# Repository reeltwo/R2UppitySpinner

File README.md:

# R2 Uppity Spinner

This is the sketch for the R2 Uppity Spinner. It depends on the Reeltwo library. You can download the latest release of the Reeltwo library here: https://github.com/reeltwo/Reeltwo/releases

Default baud rate is 9600 baud and the default I2C address is 32 (0x20). Both can be changed using the configuration commands below.

After installing your board you should run the `#PSC` calibration command.

If you want a snappy hyper caffinated periscope you should use a 6V lifter motor. If you want a slower more deliberate periscope you should use a 12V lifter motor.

# Assembling R2 Uppity Spinner PCB Part 1

# Assembling R2 Uppity Spinner PCB Part 2

## Configure commands

`#PSC`:
Calibration routine. Will store results in EEPROM if successful
*Examples*:

    #PSC

`#PZERO`:
Erase all stored sequences from EEPROM
*Examples*:

    #PZERO

`#PL`:
List all stored sequences
*Examples*:

    #PL

`#PD`[number]:
Delete numbered sequence from EEPROM
*Examples*:

    #PD0 (delete sequence 0)

`#PS`[number]:seq
Store specified sequence (seq) as number in EEPROM.
*Examples*:

	#PS1:H                        (periscope down)
	#PS2:P100                     (periscope up)
	#PS3:P100:L5:R30              (search light counter-clockwise)
	#PS4:P100,100:L7:M,80,80,2,4  (random fast)
	#PS5:P100:L7:M,50,40,5,5      (random slow)
	#PS6:A0                       (face forward)
	#PS7:P100:L5:R-30             (search light clockwise)
	#PS8:H:P50:W2:P85,35:A90,25:W2:A270,20,100:W2:P100,100:L5:R50:W4:H    (sneaky periscope)
	#PS0:H:L0:P100,5:W2:P50:W2:P85,35:A90,25:W2:A270,20,100:W2:P100,100:L5:R50:W4:H

`#PBAUD`[baudrate]
Change system baudrate. Settings will be stored in EEPROM and take affect once the board is reset.
*Examples*:

	#PBAUD9600               (set baud rate to 9600)

`#PI2C`[address]
Change system I2C address. Settings will be stored in EEPROM and take affect once the board is reset.
*Examples*:

	#PI2C128                 (set I2C address to 128)

`#PR`
Enable/disable rotary unit. This will reboot the board. The setting will persist between reboots.
*Examples*:

	#PR (toggle rotary unit on/off)

`#PNCL`
Set lifter limit switch to normally closed. Default setting.
*Examples*:

	#PNCL (lifter limit normally closed)

`#PNOL`
Set lifter limit switch to normally open.
*Examples*:

	#PNOL (lifter limit normally open)

`#PNCR`
Set rotary limit switch to normally closed. Default setting.
*Examples*:

	#PNCL (rotary limit normally closed)

`#PNOR`
Set rotary limit switch to normally open.
*Examples*:

	#PNOR (rotary limit normally open)

Lifter commands
===============

A lifter command starts with ':P' followed by one of the these. Multiple commands can be issued seperated by a colon. Only the first command needs to be prefixed with 'P':

	:PP100:W2:P0

Would raise the periscope. Wait 2 seconds. Lower the periscope. Separately the commnads would be:

	:PP100
	:PW2
	:PP0

### Play stored sequence

`S`[number]:
Sequences can be stored using #PS
*Examples*:

    #PS0:H:L0:P100,5:W2:P50,25:W2:P85,35:A90,20:W2:A270,20,100:W2:P100,100:L5:R50:W4:H

### Wait number of seconds
`W`[R]seconds:
Wait for specified number of seconds. If 'R' is specified it will randomize the wait time in the range of 1..seconds. 'seconds' is a number between 1 and 600.
*Examples*:

	:PW2    (wait 2 seconds before executing next sequence)
	:PWR    (wait random 1-6 seconds)
	:PWR10  (wait random 1-10 seconds)

### Light kit sequence
`L`number:
Light kit sequence where number is in the range 0..7

`0`: Full Cycle (default): This routine will randomly select the LED color, pattern, and speed for a random period of time.
    
`1`: Off: This setting turns ALL lights OFF. I added this to allow a microcontroller to turn off the lights without having to kill the supply power.
    
`2`: Obi Wan: The Top LED’s flash Blue, the Side LED’s are Blue, and the Main White LED’s are Random.
    
`3`: Yoda: The Top LED’s and Side LED’s fade Green On and Off.
    
`4`: Sith: The Top LED’s and Side LED’s flash Red.
    
`5`: Search Light: All LED’s are White, the Center Bright LED is ON.
    
`6`: Dagobah: This is the most screen accurate mode. The Main White LED’s are ON, the side LED’s are White, the Lower  Rectangular Red LED’s are All On, and the Rear LED’s are Blinking Red.
    
`7`: Sparkle: All White LED’s randomly Flash
    
*Examples*:

    :PL0    (full cycle)
    :PL1    (off)

### Home
`H`[speed]:
Rotates the periscope into the home position and lowers the lifter. Will retry once if rotary ends up not in home position.
*Examples*:

	:PH     (go home at minimum power)
	:PH50   (go home at 50% speed)
	:PH100  (go home at 100% speed)

### Rotate scope relative degrees
`D`[R]:
Rotate scope random relative degrees
*Examples*:

	:PDR

`D`[degrees]:
Rotate scope relative degrees positive for counter clockwise and negative for clockwise
*Examples*:

	:PD90       (rotate periscope relative 90 degrees counter clockwise)
	:PD-90      (rotate periscope relative 90 degrees clockwise)

### Rotate scope absolute degrees
`A`[R][,speed][,maxspeed]:
Rotate scope random absolute degrees
*Examples*:

	:PAR

`A`[degrees][,speed][,maxspeed]:
Rotate scope to absolute position degrees. Positive for clockwise and negative for counter clockwise. Optionally specify the speed percentage and maximum speed percentage. By default the speed used is minimum rotary power (20%). The maximum speed defaults to the same value as speed if omitted.
*Examples*:

	:PA90        (rotate periscope to 90 degrees clockwise)
	:PA270       (rotate periscope to 270 degrees clockwise)
	:PA-90       (rotate periscope to 270 degrees clockwise)
	:PA0         (rotate periscope to home position)
	:PA90,20,100 (rotate periscope to 90 degrees starting at 20% speed increasing to 100%)
	             (will mostly likely overshoot target)

### Rotate scope continously
`R`[speed]:
Spin rotary scope at specified speed percentage
*Examples*:

	:PR30       (spin periscope at 30% speed counter clockwise)
	:PR-30      (spin periscope at 30% speed clockwise)

`R`[,speed]:
Lift periscope to random position.
*Examples*:

	:PPR        (random position)
	:PPR,50     (random position at 50% speed)

### Raise/lower periscope
`P`[position][,speed]:
Lift periscope to specified position percentage.
*Examples*:

	:PP100      (raise periscope fully)
	:PP0        (lower periscope fully)
	:PP50       (raise periscope halfway)
	:PP100,100  (raise periscope fully at maximum speed)

### Movement Random Continous
`M`,lifterspeed][,rotaryspeed][,mininterval][,maxinterval]:
Animate periscope continously rotate/lift.
*Examples*:

	:M,80,80,2,4  (animate lifter 80% power, rotatary random(20%-80%), minimum interval 2 seconds for a duration of 2+random(4) seconds )
	:M,50,40,5,5  (animate lifter 50% power, rotatary random(20%-40%) power, 80% minimum interval 5 seconds for a duration of 5+5 seconds )

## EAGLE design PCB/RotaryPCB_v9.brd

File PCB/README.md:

# Electronics Design

The files were created using Fusion 360, which uses a new version of the Eagle format.

- LifterPCB.brd
- LifterPCB.sch

- RotaryPCB.brd
- RotaryPCB.sch

These files were exported in Eagle v9 compatible format.

- LifterPCB_v9.brd
- LifterPBC_v9.sch

- RotaryPCB_v9.brd
- RotaryPCB_v9.sch

This version uses thicker traces and adds a copper pour. The lifter board is a four layer board. The order of the connection pins on the rotary has changed. Do NOT use the same cable as the older board. The order was changed to allow using a silicone ribbon cable and this crimp connector:

https://www.mouser.com/ProductDetail/571-2-1761607-3

The 10 Wire silicone cable:
https://www.adafruit.com/product/3890

The dual row IDC female connectors:
https://www.amazon.com/gp/product/B07S1NFG4S

If you do not plan on using the ribbon cable there is no need to switch to this version of the lifter.

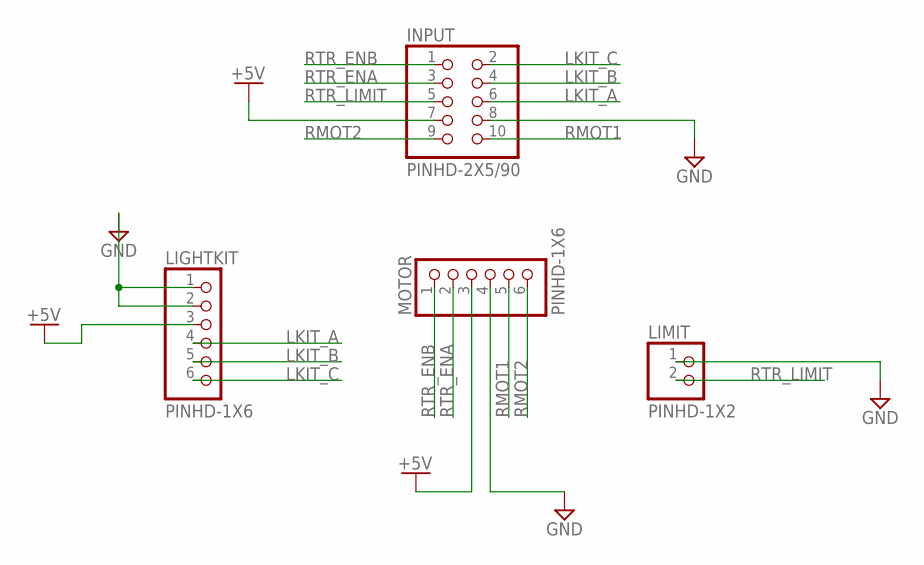
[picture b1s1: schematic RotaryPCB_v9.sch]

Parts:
INPUT: PINHD-2X5/90; 2X05/90
LIGHTKIT: PINHD-1X6; 1X06
LIMIT: PINHD-1X2; 1X02
MOTOR: PINHD-1X6; 1X06

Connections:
+5V: INPUT.7, LIGHTKIT.3, MOTOR.3
GND: INPUT.8, LIGHTKIT.1, LIGHTKIT.2, LIMIT.1, MOTOR.4
LKIT_A: INPUT.6, LIGHTKIT.4
LKIT_B: INPUT.4, LIGHTKIT.5
LKIT_C: INPUT.2, LIGHTKIT.6
RMOT1: INPUT.10, MOTOR.5
RMOT2: INPUT.9, MOTOR.6
RTR_ENA: INPUT.3, MOTOR.2
RTR_ENB: INPUT.1, MOTOR.1
RTR_LIMIT: INPUT.5, LIMIT.2

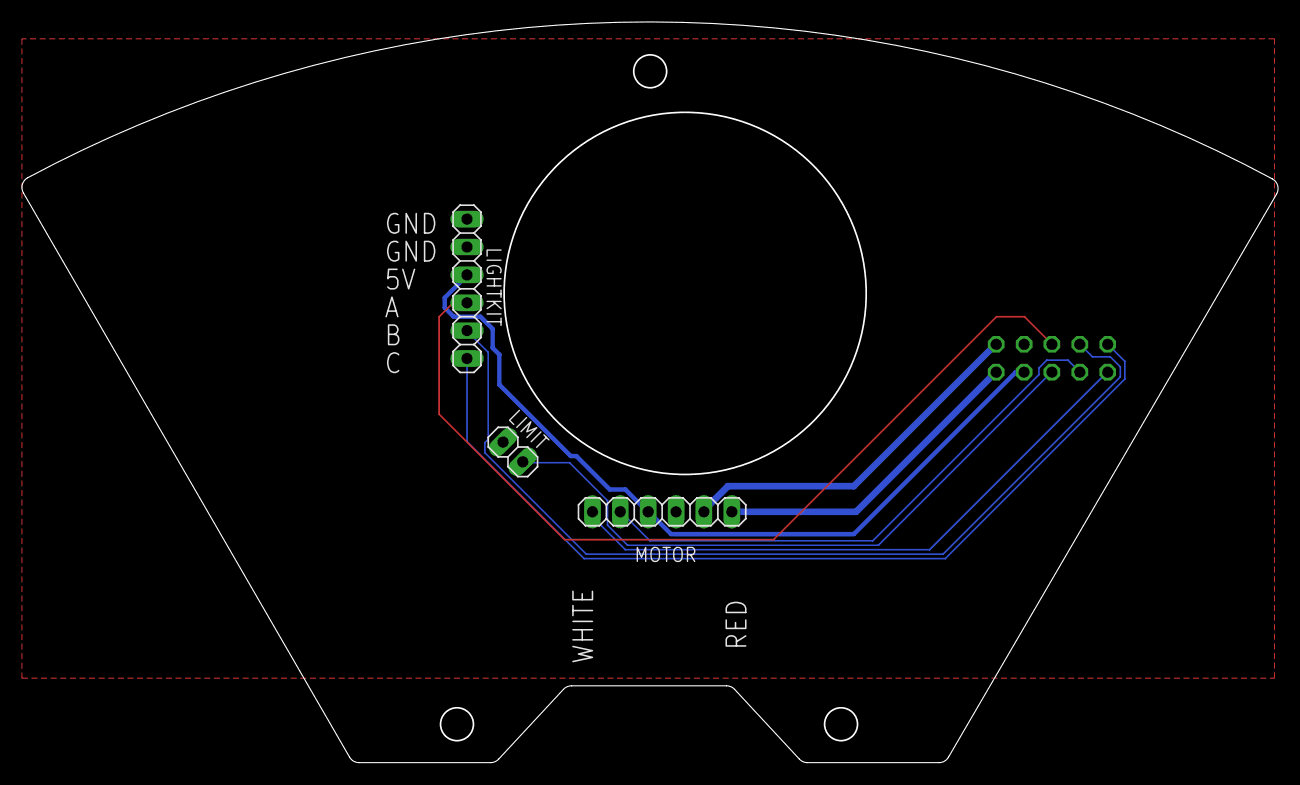
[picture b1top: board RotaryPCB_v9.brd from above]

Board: 2 copper layers, 114.5 x 67.5 mm, 4 parts (1 on the bottom side), 10 nets.

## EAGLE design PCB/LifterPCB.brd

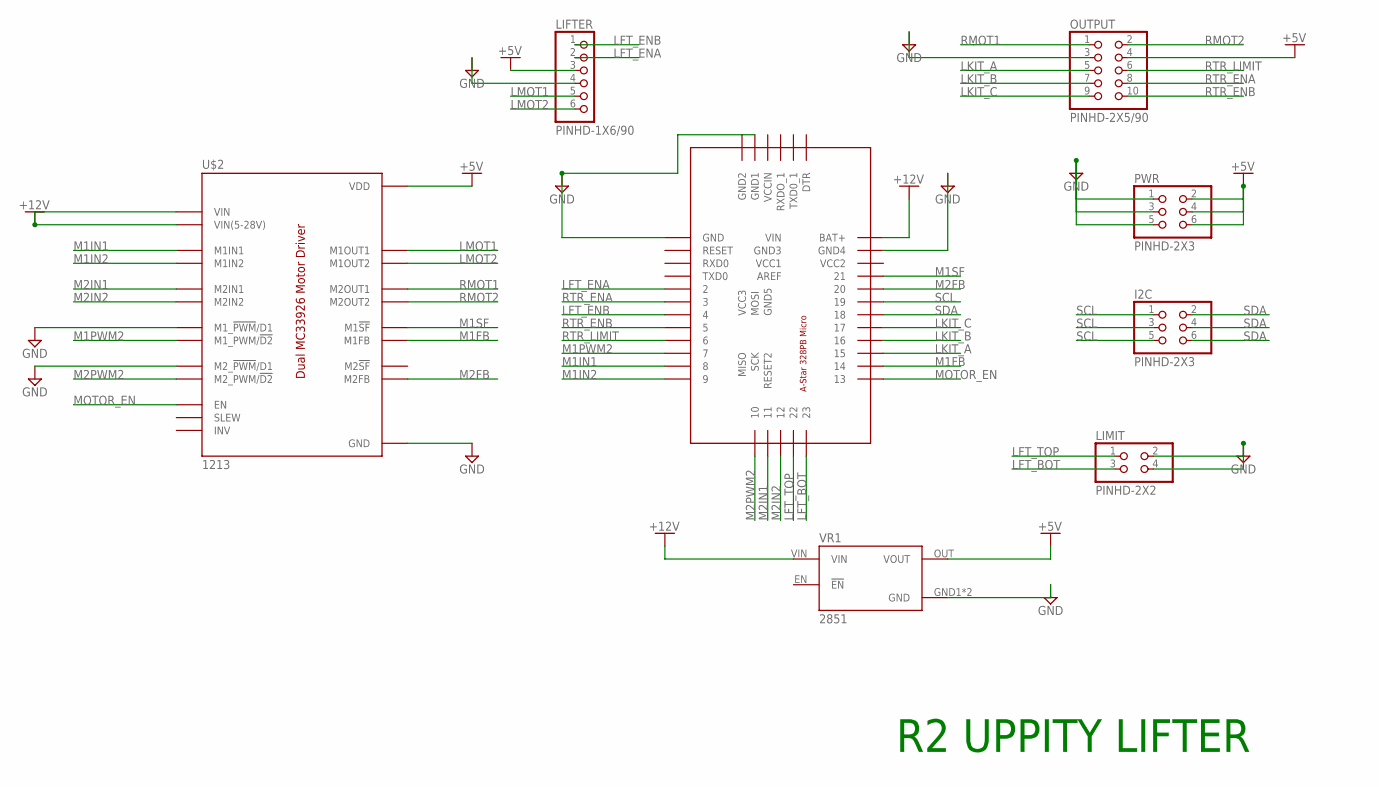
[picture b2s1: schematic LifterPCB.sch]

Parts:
I2C: PINHD-2X3; 2X03
LIFTER: PINHD-1X6/90; 1X06/90
LIMIT: PINHD-2X2; 2X02
OUTPUT: PINHD-2X5/90; 2X05/90
PWR: PINHD-2X3; 2X03
U$1: POLOLU3161
U$2: 1213
VR1: 2851; VREG_2851

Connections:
+5V: LIFTER.3, OUTPUT.4, PWR.2, PWR.4, PWR.6, U$2.VDD, U$2.VDD$1 (VDD), U$2.VDD$2 (VDD), U$2.VDD$3 (VDD), U$2.VDD$4 (VDD), U$2.VDD$5 (VDD), VR1.OUT (VOUT)
+12V: U$1.BAT+, U$2.MVIN (VIN(5-28V)), U$2.VIN, VR1.VIN
GND: LIFTER.4, LIMIT.2, LIMIT.4, OUTPUT.3, PWR.1, PWR.3, PWR.5, U$1.GND2 (GND4), U$1.GND4 (GND2), U$1.GND5 (GND1), U$1.GND6 (GND), U$2.GND, U$2.GND$1 (GND), U$2.GND$2 (GND), U$2.M1PWM1 (M1_!PWM!/D1), U$2.M2PWM1 (M2_!PWM!/D1), U$2.MGND (GND), VR1.GND1 (GND), VR1.GND2 (GND)
LFT_BOT: LIMIT.3, U$1.23
LFT_ENA: LIFTER.2, U$1.2
LFT_ENB: LIFTER.1, U$1.4
LFT_TOP: LIMIT.1, U$1.22
LKIT_A: OUTPUT.5, U$1.15
LKIT_B: OUTPUT.7, U$1.16
LKIT_C: OUTPUT.9, U$1.17
LMOT1: LIFTER.5, U$2.M1OUT1
LMOT2: LIFTER.6, U$2.M1OUT2
M1FB: U$1.14, U$2.M1FB
M1IN1: U$1.8, U$2.M1IN1
M1IN2: U$1.9, U$2.M1IN2
M1PWM2: U$1.7, U$2.M1PWM2 (M1_PWM/!D2)
M1SF: U$1.21, U$2.M1SF (M1!SF)
M2FB: U$1.20, U$2.M2FB
M2IN1: U$1.11$1 (11), U$2.M2IN1
M2IN2: U$1.12$1 (12), U$2.M2IN2
M2PWM2: U$1.10, U$2.M2PWM2 (M2_PWM/!D2)
MOTOR_EN: U$1.13$1 (13), U$2.EN
RMOT1: OUTPUT.1, U$2.M2OUT1
RMOT2: OUTPUT.2, U$2.M2OUT2
RTR_ENA: OUTPUT.8, U$1.3
RTR_ENB: OUTPUT.10, U$1.5
RTR_LIMIT: OUTPUT.6, U$1.6
SCL: I2C.1, I2C.3, I2C.5, U$1.19
SDA: I2C.2, I2C.4, I2C.6, U$1.18

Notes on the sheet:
R2 UPPITY LIFTER

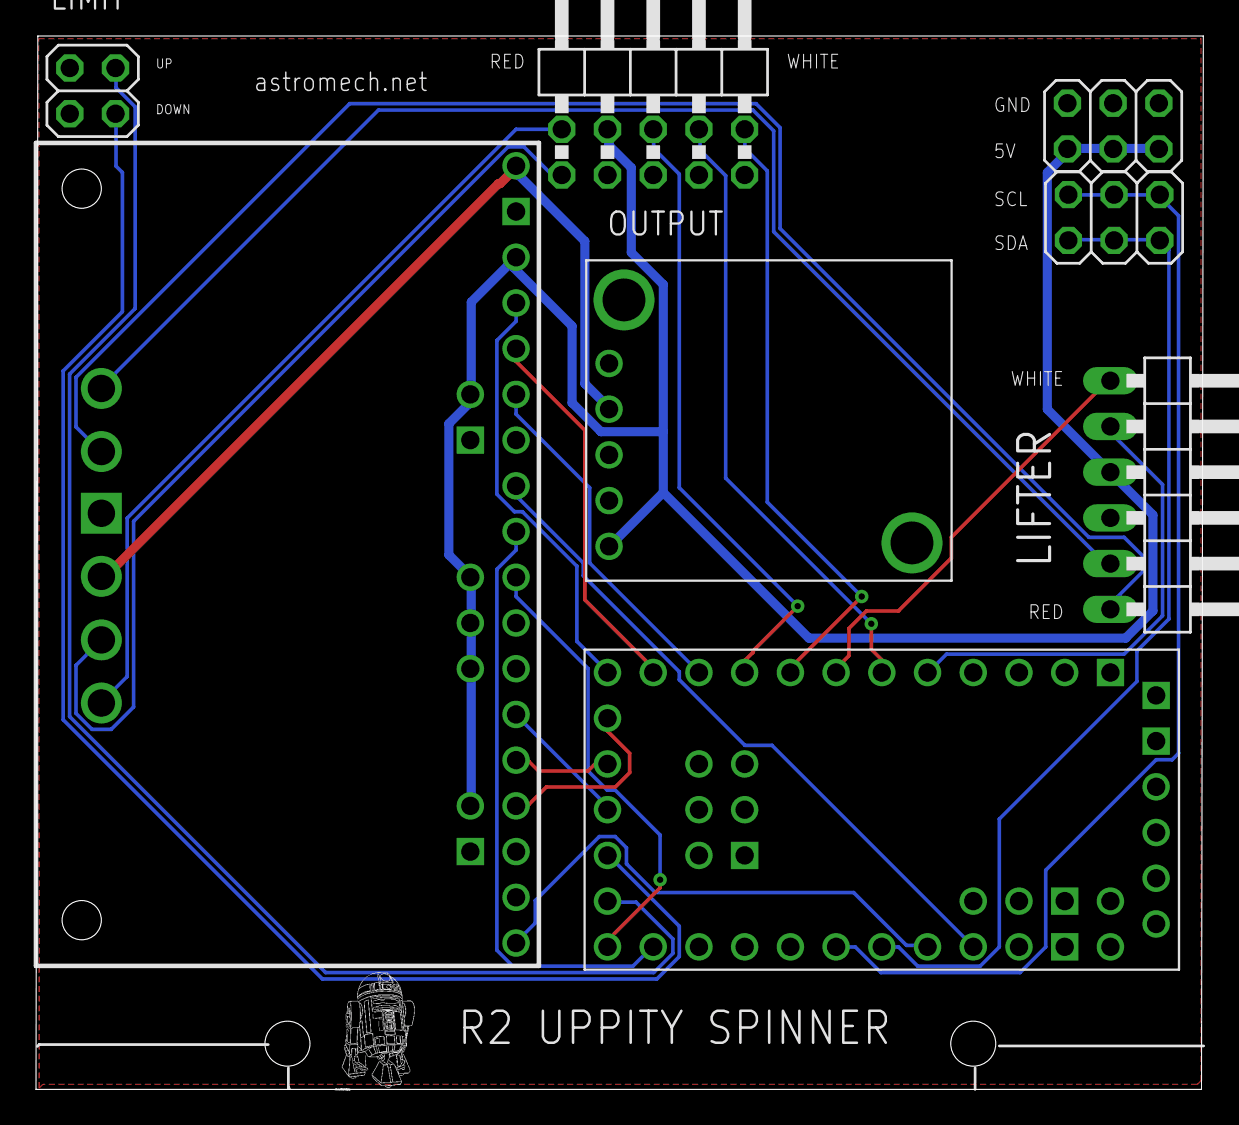
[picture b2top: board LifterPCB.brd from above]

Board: 4 copper layers, 64.9 x 58.5 mm, 8 parts (0 on the bottom side), 29 nets.

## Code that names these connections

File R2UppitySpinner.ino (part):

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#define PIN_LIFTER_ENCODER_A   2
#define PIN_LIFTER_ENCODER_B   4

#define PIN_M1SF               A7
#define PIN_M2FB               A6

#define PIN_LIFTER_TOPLIMIT    23
#define PIN_LIFTER_BOTLIMIT    22
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#define PIN_MOTORS_EN          13   /* also BUILTIN_LED */
#define PIN_M1D2               7
#define PIN_M1PWM1             8
#define PIN_M1PWM2             9
#define PIN_M1FB               A0

///////////////////////////////////
// --- Rotary mechanism
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/* Rotary Motor */
#define PIN_M2D2               10
#define PIN_M2PWM1             11
#define PIN_M2PWM2             12

//////////////////////////////
// LIGHT KIT TRI-STATE
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
    static bool lifterMotorFault()
    {
        return !digitalRead(PIN_M1SF);
    }

    static int lifterMotorCurrent()
    {
        // 5V / 10bit resolution / 0.525V/A = 0.0093006 A/count ~= 93 mA/count
        return analogRead(PIN_M1FB) * 93;
    }

    static int rotaryMotorCurrent()
    {
        // 5V / 10bit resolution / 0.525V/A = 0.0093006 A/count ~= 93 mA/count
        return analogRead(PIN_M2FB) * 93;
    }

    static bool isIdle()
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            if (reverse)
            {
                analogWrite(PIN_M1PWM1, 255);
                analogWrite(PIN_M1PWM2, 255 - (255 * throttle));
                fLifterThrottle = -throttle;
            }
            else
            {
                analogWrite(PIN_M1PWM1, 0);
                analogWrite(PIN_M1PWM2, 255 * throttle);
                fLifterThrottle = throttle;
            }
            digitalWrite(PIN_M1D2, HIGH);
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    {
        enableMotors();
        analogWrite(PIN_M1PWM1, 0);
        analogWrite(PIN_M1PWM2, 0);
        digitalWrite(PIN_M1D2, HIGH);
        fLifterThrottle = 0;
    }
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                if (reverse)
                {
                    analogWrite(PIN_M2PWM1, 255 - (255 * throttle));
                    analogWrite(PIN_M2PWM2, 255);
                    fRotaryThrottle = -throttle;
                }
                else
                {
                    analogWrite(PIN_M2PWM1, 255 * throttle);
                    analogWrite(PIN_M2PWM2, 0);
                    fRotaryThrottle = throttle;
                }
                digitalWrite(PIN_M2D2, HIGH);
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        fRotarySpeed = 0;
        enableMotors();
        analogWrite(PIN_M2PWM1, 0);
        analogWrite(PIN_M2PWM2, 0);
        digitalWrite(PIN_M2D2, HIGH);
        fRotaryThrottle = 0;
        fRotaryMoving = false;
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        // LIFTER
        pinMode(PIN_M1D2, OUTPUT);
        pinMode(PIN_M1PWM1, OUTPUT);
        pinMode(PIN_M1PWM2, OUTPUT);
        digitalWrite(PIN_M1D2, LOW);

        // ROTARY
        pinMode(PIN_M2D2, OUTPUT);
        pinMode(PIN_M2PWM1, OUTPUT);
        pinMode(PIN_M2PWM2, OUTPUT);
        digitalWrite(PIN_M2D2, LOW);

        // FEEDBACK ONLY FOR LIFTER
        pinMode(PIN_M1FB, INPUT);
        pinMode(PIN_M2FB, INPUT);
        pinMode(PIN_M1SF, INPUT_PULLUP);

        //////////////////////////
        // LIGHT KIT PINS
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                encoder_rotary_stop_ticks = encoder_rotary_ticks;
                // Stop rotary motor if limit switch was hit
                analogWrite(PIN_M2PWM1, 0);
                analogWrite(PIN_M2PWM2, 0);
                digitalWrite(PIN_M2D2, HIGH);
            }
        }
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
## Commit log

2021-06-02 Initial release
2021-06-02 Added board files
2021-06-02 Added configuration commands #PBAUD and #PI2C to set the baudrate and I2C address
2021-06-10 Generalized the motor stall detection and added to all loops. Fixed homing sequence to be more reliable. Added enthropy to random numbers.
2021-06-11 Latest version of Eagle board files plus Eagle v9 version
2021-06-20 Added support for continous random mode
2021-06-20 Clean up
2021-06-20 Clean up and changed default baud rate to 9600
2021-06-21 Allow wait and light kit commands during move mode
2021-06-27 Added commands PNCL, PNOL, PNCR, and PNOR. To change the type of limit switch wiring. Normally the limit switches should be wired NC. Meaning that digitalRead() will return 0 if the limit switch is t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
2021-08-27 Improved calibration routine
2021-09-14 Fixed listing of stored sequences
2021-10-20 Added support for DISABLE_ROTARY for builders making their own custom lifters. Fixed support for I2C IA-Parts style commands.
2021-10-20 This version uses thicker traces and adds a copper pour. The lifter board is a four layer board. The order of the connection pins on the rotary has changed. Do NOT use the same cable as the older boa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
2022-01-17 Enabled USE_DEBUG by disabling EEPROM features
2022-01-20 Update README.md
    Added video links showing assembly of PCB
2022-02-17 Added PS8 animation. Sneaky periscope
2022-03-10 Added video link to README
2022-03-15 Added #PR command to enable/disable rotary unit
2022-03-15 Update README.md
    Fixed incorrect command in README
2022-03-29 Fixed bug in rotate relative which would only rotate in one direction because it normalized the parameter. Simplified the code so the relative rotation just calls the absolute rotation code after cal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
2022-03-29 Lifter wouldn't lifter slower than minimum power and never called seekToPositionSlow()
2022-04-04 Update README.md
    Fixed missing 'W' in wait command example
